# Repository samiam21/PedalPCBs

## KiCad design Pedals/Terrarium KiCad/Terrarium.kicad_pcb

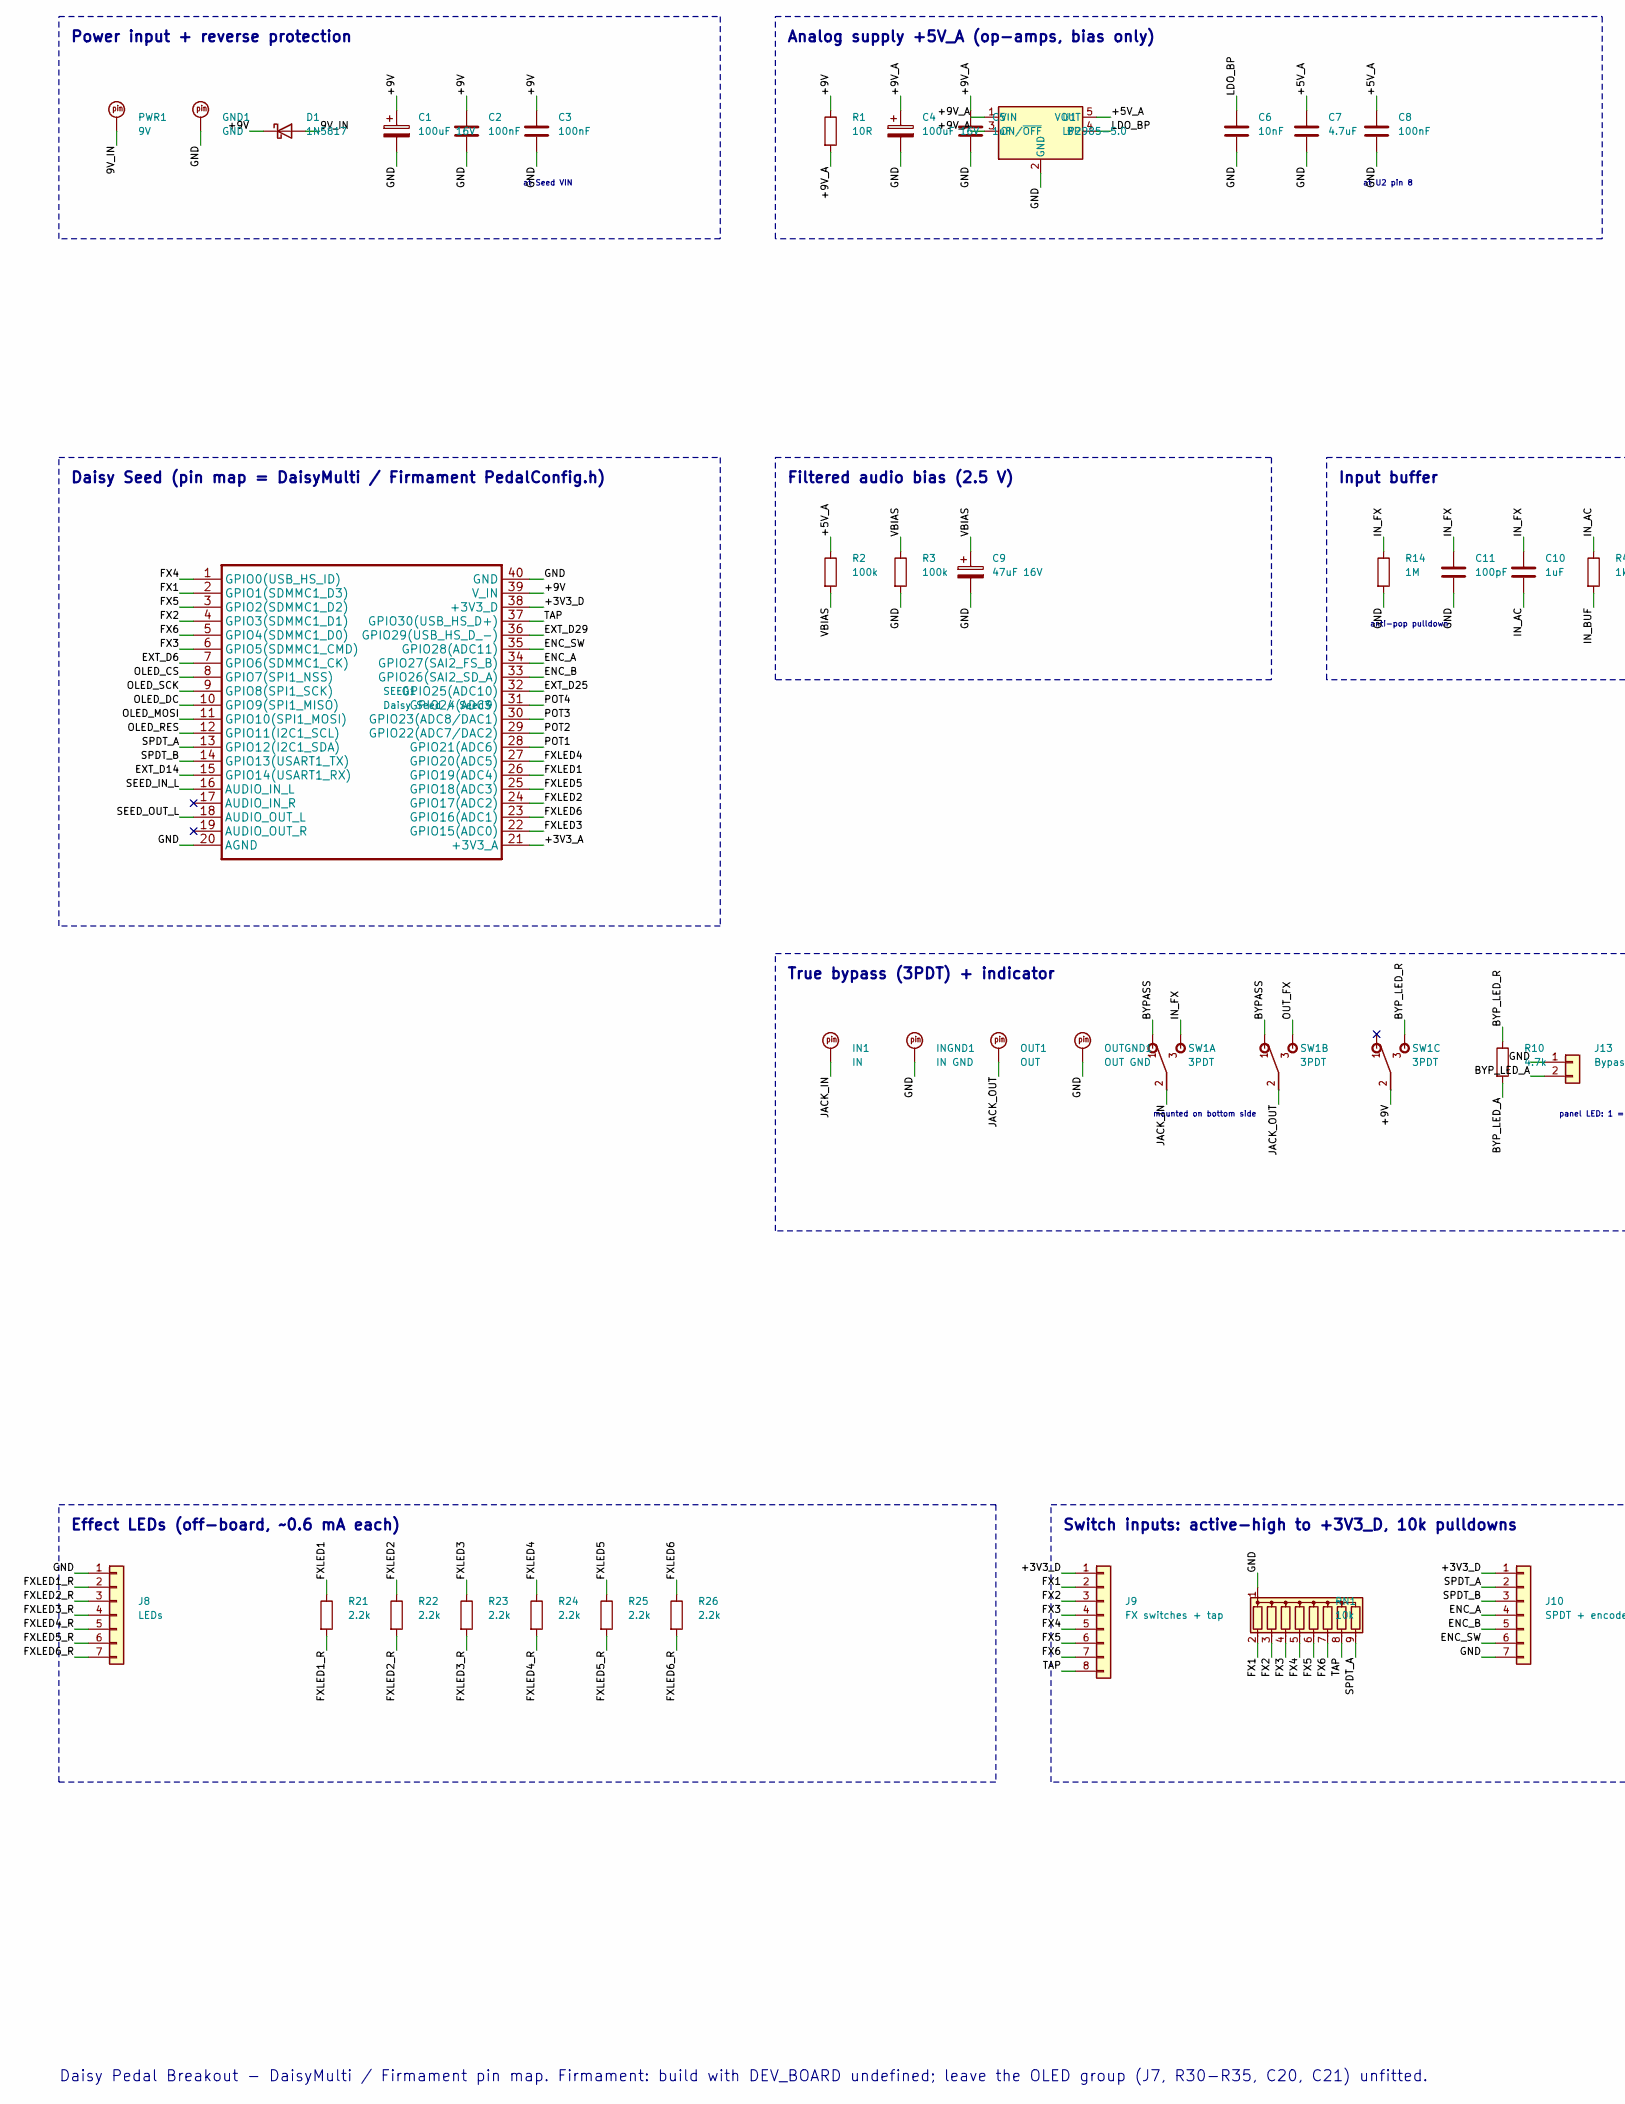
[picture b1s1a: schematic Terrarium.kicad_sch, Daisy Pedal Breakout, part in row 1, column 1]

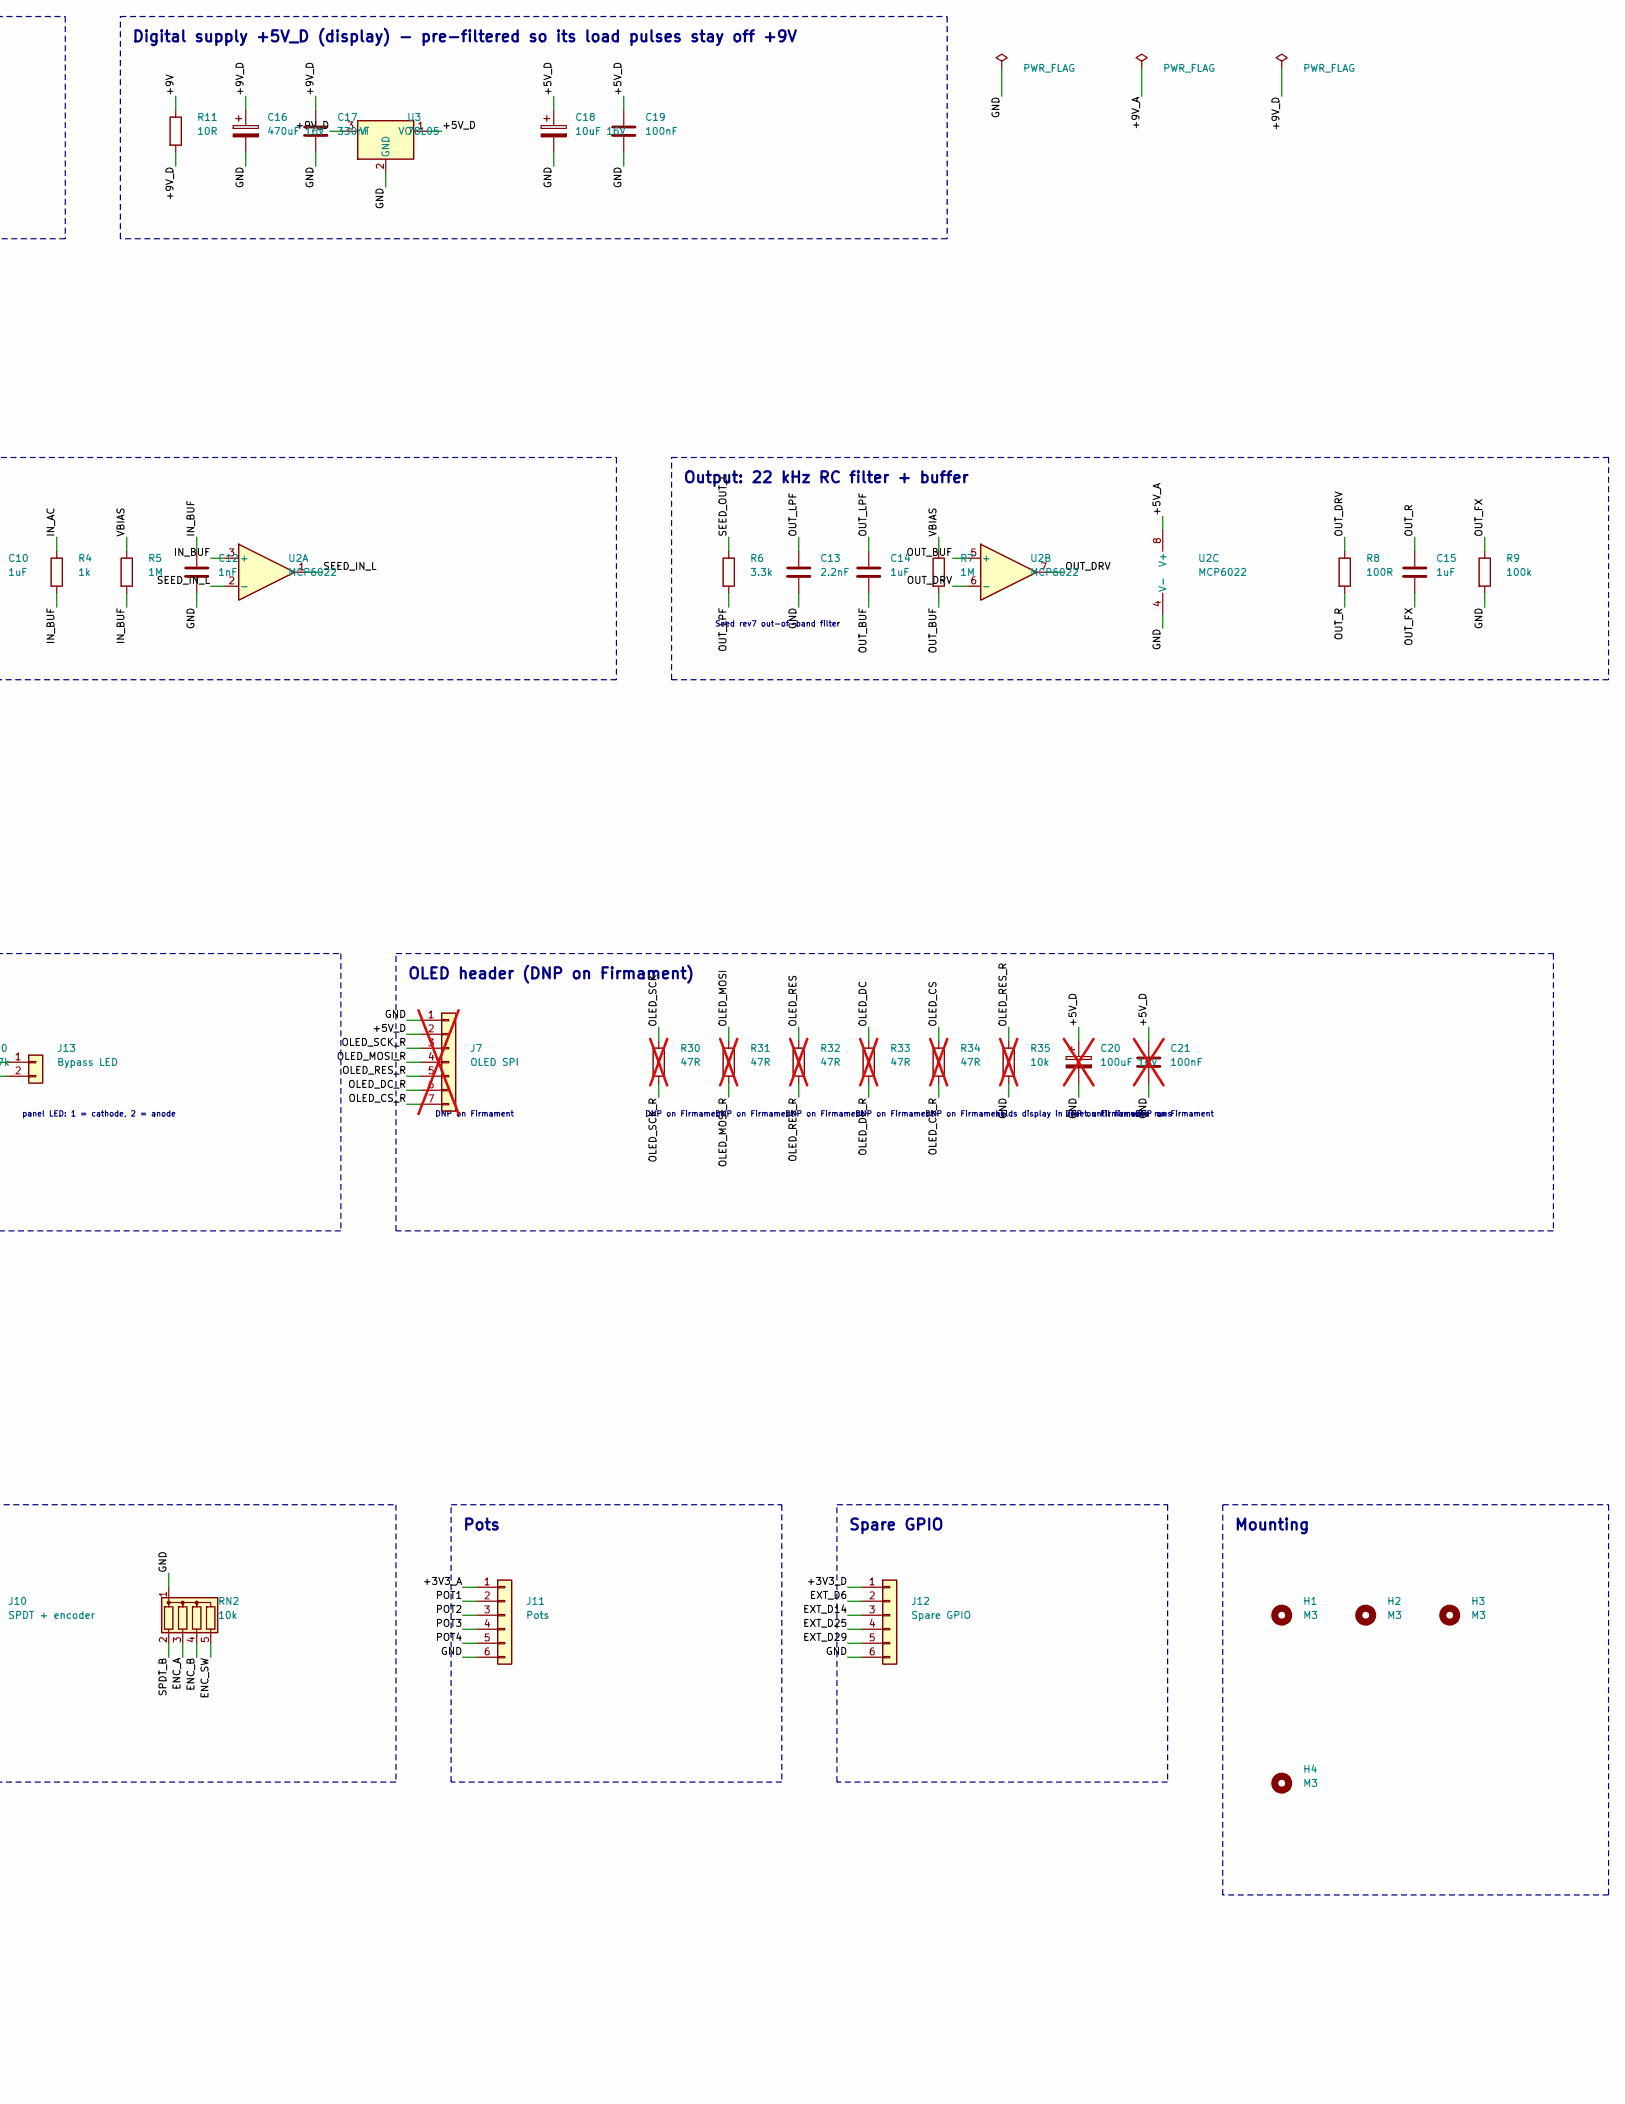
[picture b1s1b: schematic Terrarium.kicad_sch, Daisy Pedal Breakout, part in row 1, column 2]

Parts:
C1, C4: 100uF 16V; CP_Radial_D6.3mm_P2.50mm
C2, C3: 100nF; C_Disc_D5.0mm_W2.5mm_P5.00mm
C5: 1uF; C_Disc_D3.0mm_W1.6mm_P2.50mm
C6: 10nF; C_Disc_D3.0mm_W1.6mm_P2.50mm
C7: 4.7uF; C_Disc_D3.0mm_W1.6mm_P2.50mm
C8, C19: 100nF; C_Disc_D3.0mm_W1.6mm_P2.50mm
C9: 47uF 16V; CP_Radial_D5.0mm_P2.00mm
C10, C14, C15: 1uF; C_Rect_L7.2mm_W4.5mm_P5.00mm_FKS2_FKP2_MKS2_MKP2
C11: 100pF; C_Disc_D3.0mm_W1.6mm_P2.50mm
C12: 1nF; C_Disc_D3.0mm_W1.6mm_P2.50mm
C13: 2.2nF; C_Disc_D5.0mm_W2.5mm_P5.00mm
C16: 470uF 16V; CP_Radial_D8.0mm_P3.50mm
C17: 330nF; C_Disc_D5.0mm_W2.5mm_P5.00mm
C18: 10uF 16V; CP_Radial_D5.0mm_P2.00mm
C20: 100uF 16V; CP_Radial_D6.3mm_P2.50mm; not fitted
C21: 100nF; C_Disc_D3.0mm_W1.6mm_P2.50mm; not fitted
D1: 1N5817; D_DO-41_SOD81_P10.16mm_Horizontal
GND1: GND; UNLABELED
H1, H2, H3, H4: M3; MountingHole_3.2mm_M3
IN1: IN; UNLABELED
INGND1: IN GND; UNLABELED
J7: OLED SPI; PinHeader_1x07_P2.54mm_Vertical; not fitted
J8: LEDs; PinHeader_1x07_P2.54mm_Vertical
J9: FX switches + tap; PinHeader_1x08_P2.54mm_Vertical
J10: SPDT + encoder; PinHeader_1x07_P2.54mm_Vertical
J11: Pots; PinHeader_1x06_P2.54mm_Vertical
J12: Spare GPIO; PinHeader_1x06_P2.54mm_Vertical
J13: Bypass LED; PinHeader_1x02_P2.54mm_Vertical
OUT1: OUT; UNLABELED
OUTGND1: OUT GND; UNLABELED
PWR1: 9V; UNLABELED
R1, R11: 10R; R_Axial_DIN0207_L6.3mm_D2.5mm_P7.62mm_Horizontal
R2, R3, R9: 100k; R_Axial_DIN0207_L6.3mm_D2.5mm_P7.62mm_Horizontal
R4: 1k; R_Axial_DIN0207_L6.3mm_D2.5mm_P7.62mm_Horizontal
R5, R7, R14: 1M; R_Axial_DIN0207_L6.3mm_D2.5mm_P7.62mm_Horizontal
R6: 3.3k; R_Axial_DIN0207_L6.3mm_D2.5mm_P7.62mm_Horizontal
R8: 100R; R_Axial_DIN0207_L6.3mm_D2.5mm_P7.62mm_Horizontal
R10: 4.7k; R_Axial_DIN0207_L6.3mm_D2.5mm_P7.62mm_Horizontal
R21, R22, R23, R24, R25, R26: 2.2k; R_Axial_DIN0207_L6.3mm_D2.5mm_P7.62mm_Horizontal
R30, R31, R32, R33, R34: 47R; R_Axial_DIN0207_L6.3mm_D2.5mm_P2.54mm_Vertical; not fitted
R35: 10k; R_Axial_DIN0207_L6.3mm_D2.5mm_P2.54mm_Vertical; not fitted
RN1: 10k; R_Array_SIP9
RN2: 10k; R_Array_SIP5
SEED1: Daisy Seed / Seed3; ES_DAISY_SEED
SW1: 3PDT; 3PDT2
U1: LP2985-5.0; SOT-23-5
U2: MCP6022; DIP-8_W7.62mm
U3: 78L05; TO-92_Inline

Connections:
/9V_IN: D1.2 (A), PWR1.P$1
/+3V3_A: J11.1, SEED1.21 (+3V3_A)
/+3V3_D: J9.1, J10.1, J12.1, SEED1.38 (+3V3_D)
/+5V_A: C7.1, C8.1, R2.1, U1.5 (VOUT), U2.8 (V+)
/+5V_D: C18.1, C19.1, C20.1, C21.1, J7.2, U3.1 (VO)
/+9V: C1.1, C2.1, C3.1, D1.1 (K), R1.1, R11.1, SEED1.39 (V_IN), SW1.C2 (2)
/+9V_A: C4.1, C5.1, R1.2, U1.1 (VIN), U1.3 (ON/~OFF)
/+9V_D: C16.1, C17.1, R11.2, U3.3 (VI)
/BYPASS: SW1.A1 (1), SW1.B1 (1)
/BYP_LED_A: J13.2, R10.2
/BYP_LED_R: R10.1, SW1.C3 (3)
/ENC_A: J10.4, RN2.3 (R2), SEED1.34 (GPIO27(SAI2_FS_B))
/ENC_B: J10.5, RN2.4 (R3), SEED1.33 (GPIO26(SAI2_SD_A))
/ENC_SW: J10.6, RN2.5 (R4), SEED1.35 (GPIO28(ADC11))
/EXT_D6: J12.2, SEED1.7 (GPIO6(SDMMC1_CK))
/EXT_D14: J12.3, SEED1.15 (GPIO14(USART1_RX))
/EXT_D25: J12.4, SEED1.32 (GPIO25(ADC10))
/EXT_D29: J12.5, SEED1.36 (GPIO29(USB_HS_D_-))
/FX1: J9.2, RN1.2 (R1), SEED1.2 (GPIO1(SDMMC1_D3))
/FX2: J9.3, RN1.3 (R2), SEED1.4 (GPIO3(SDMMC1_D1))
/FX3: J9.4, RN1.4 (R3), SEED1.6 (GPIO5(SDMMC1_CMD))
/FX4: J9.5, RN1.5 (R4), SEED1.1 (GPIO0(USB_HS_ID))
/FX5: J9.6, RN1.6 (R5), SEED1.3 (GPIO2(SDMMC1_D2))
/FX6: J9.7, RN1.7 (R6), SEED1.5 (GPIO4(SDMMC1_D0))
/FXLED1: R21.1, SEED1.26 (GPIO19(ADC4))
/FXLED1_R: J8.2, R21.2
/FXLED2: R22.1, SEED1.24 (GPIO17(ADC2))
/FXLED2_R: J8.3, R22.2
/FXLED3: R23.1, SEED1.22 (GPIO15(ADC0))
/FXLED3_R: J8.4, R23.2
/FXLED4: R24.1, SEED1.27 (GPIO20(ADC5))
/FXLED4_R: J8.5, R24.2
/FXLED5: R25.1, SEED1.25 (GPIO18(ADC3))
/FXLED5_R: J8.6, R25.2
/FXLED6: R26.1, SEED1.23 (GPIO16(ADC1))
/FXLED6_R: J8.7, R26.2
/GND: C1.2, C2.2, C3.2, C4.2, C5.2, C6.2, C7.2, C8.2, C9.2, C11.2, C12.2, C13.2, C16.2, C17.2, C18.2, C19.2, C20.2, C21.2, GND1.P$1, INGND1.P$1, J7.1, J8.1, J10.7, J11.6, J12.6, J13.1, OUTGND1.P$1, R3.2, R9.2, R14.2, R35.2, RN1.1 (common), RN2.1 (common), SEED1.20 (AGND), SEED1.40 (GND), U1.2 (GND), U2.4 (V-), U3.2 (GND)
/IN_AC: C10.2, R4.1
/IN_BUF: C12.1, R4.2, R5.2, U2.3 (+)
/IN_FX: C10.1, C11.1, R14.1, SW1.A3 (3)
/JACK_IN: IN1.P$1, SW1.A2 (2)
/JACK_OUT: OUT1.P$1, SW1.B2 (2)
/LDO_BP: C6.1, U1.4 (BP)
/OLED_CS: R34.1, SEED1.8 (GPIO7(SPI1_NSS))
/OLED_CS_R: J7.7, R34.2
/OLED_DC: R33.1, SEED1.10 (GPIO9(SPI1_MISO))
/OLED_DC_R: J7.6, R33.2
/OLED_MOSI: R31.1, SEED1.11 (GPIO10(SPI1_MOSI))
/OLED_MOSI_R: J7.4, R31.2
/OLED_RES: R32.1, SEED1.12 (GPIO11(I2C1_SCL))
/OLED_RES_R: J7.5, R32.2, R35.1
/OLED_SCK: R30.1, SEED1.9 (GPIO8(SPI1_SCK))
/OLED_SCK_R: J7.3, R30.2
/OUT_BUF: C14.2, R7.2, U2.5 (+)
/OUT_DRV: R8.1, U2.6 (-), U2.7
/OUT_FX: C15.2, R9.1, SW1.B3 (3)
/OUT_LPF: C13.1, C14.1, R6.2
/OUT_R: C15.1, R8.2
/POT1: J11.2, SEED1.28 (GPIO21(ADC6))
/POT2: J11.3, SEED1.29 (GPIO22(ADC7/DAC2))
/POT3: J11.4, SEED1.30 (GPIO23(ADC8/DAC1))
/POT4: J11.5, SEED1.31 (GPIO24(ADC9))
/SEED_IN_L: SEED1.16 (AUDIO_IN_L), U2.1, U2.2 (-)
/SEED_OUT_L: R6.1, SEED1.18 (AUDIO_OUT_L)
/SPDT_A: J10.2, RN1.9 (R8), SEED1.13 (GPIO12(I2C1_SDA))
/SPDT_B: J10.3, RN2.2 (R1), SEED1.14 (GPIO13(USART1_TX))
/TAP: J9.8, RN1.8 (R7), SEED1.37 (GPIO30(USB_HS_D+))
/VBIAS: C9.1, R2.2, R3.1, R5.1, R7.1

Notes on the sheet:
at Seed VIN
Power input + reverse protection
at U2 pin 8
Analog supply +5V_A (op-amps, bias only)
Digital supply +5V_D (display) - pre-filtered so its load pulses stay off +9V
Daisy Seed (pin map = DaisyMulti / Firmament PedalConfig.h)
Filtered audio bias (2.5 V)
anti-pop pulldown
Input buffer
Seed rev7 out-of-band filter
Output: 22 kHz RC filter + buffer
mounted on bottom side
panel LED: 1 = cathode, 2 = anode
True bypass (3PDT) + indicator
DNP on Firmament
holds display in reset until firmware runs
OLED header (DNP on Firmament)
Effect LEDs (off-board, ~0.6 mA each)
Switch inputs: active-high to +3V3_D, 10k pulldowns
Pots
Spare GPIO
Mounting
Daisy Pedal Breakout - DaisyMulti / Firmament pin map. Firmament: build with DEV_BOARD undefined; leave the OLED group (J7, R30-R35, C20, C21) unfitted.

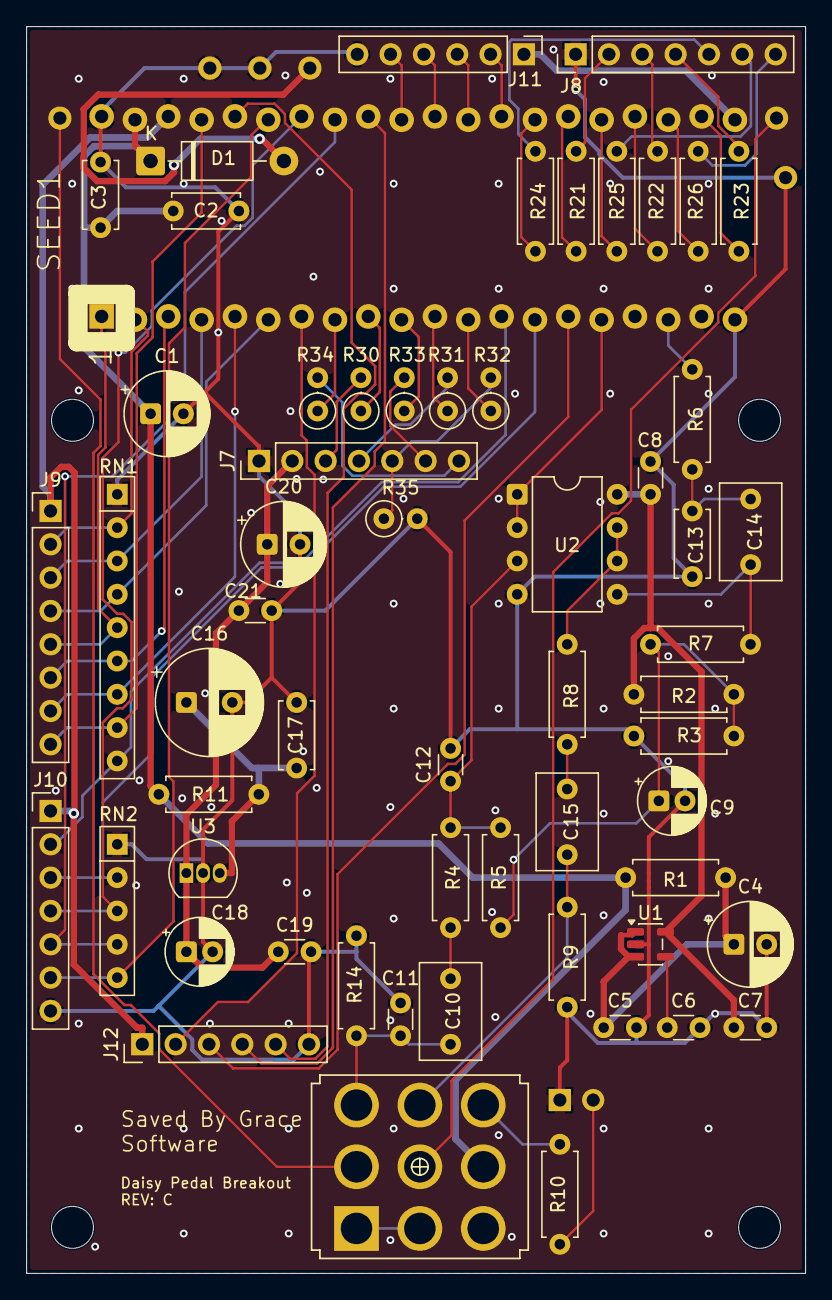
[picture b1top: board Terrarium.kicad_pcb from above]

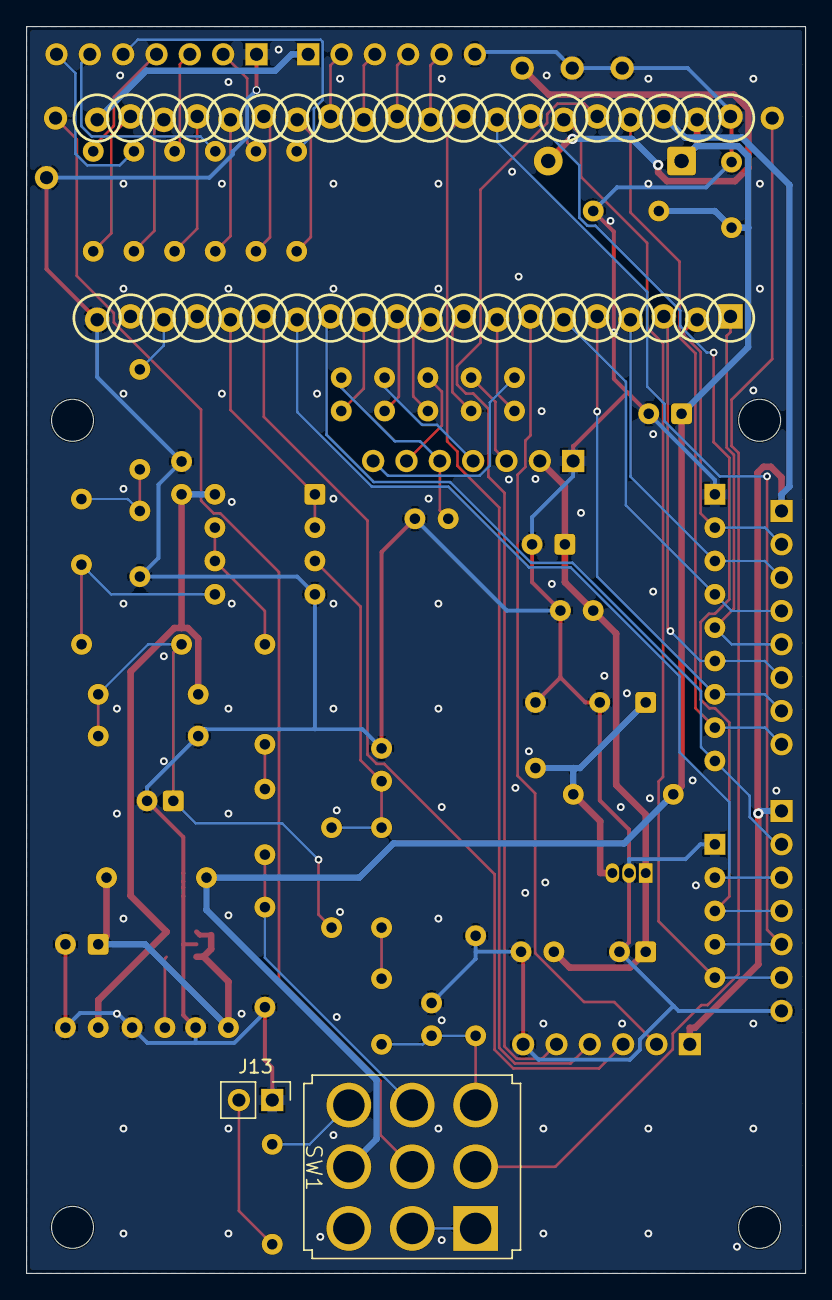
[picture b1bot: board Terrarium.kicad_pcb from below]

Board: 2 copper layers, 59.4 x 95.0 mm, 70 parts (2 on the bottom side), 68 nets.

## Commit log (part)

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2021-03-31 Add eagle libraries and initial zdrive
2021-03-31 Update zdrive schematic with new pots
2021-03-31 Add zdrive reference docs
2021-03-31 Update schematic and begin board layout
2021-03-31 Working on layout
2021-04-01 Remove accidental folder commit
2021-04-01 Adding switch for capacitor
2021-04-01 Working on board layout
2021-04-07 Restarting board design...
2021-04-07 Re-add reference docs
2021-04-13 Working on routing
2021-04-13 Board routed V1
2021-04-15 Shift switch
2021-04-16 Adjusted the pots
2021-04-19 Rotate switch
2021-04-22 Shift pots so they are centered
2021-04-22 Update silkscreen
2021-04-28 Add bypass schematic
2021-04-28 Route board
2021-05-10 Update switch to correct footprint size
2021-05-11 Switch pots to bottom and add gnd plane
2021-05-12 Flip top pots
2021-05-12 Flip bottom pots
2021-05-12 Push to Fusion
2021-06-11 Flipped the volume and tone pots
2021-06-11 Fix labels on board
2021-06-11 Move resistor for greater impact of switch
2021-07-27 Add parts to library
2021-07-27 Add digilent schematic
2021-07-27 Add grounding planes
2021-07-27 Round corners
2021-07-27 Update board label
2021-08-17 Add Analog Discovery 2 header to library
2021-08-23 DP-97 - Move breakout board to this repo
2021-08-23 DP-97 - Update with wave analysis board
2021-08-23 DP-97 - Add DIP switch to library
2021-09-29 Put correct header on the digilent PCB
2021-09-29 DP-97 - Update multi-effect grounding scheme
2021-09-29 DP-97 - Finish updating grounding scheme on multi-effect pedal
2021-10-06 DP-97 - Add power conditioning caps to 3V3_D
2023-03-11 Updated to larger cap footprints for Headmaster
2023-03-27 Removed transistors
2023-03-29 Add Electrosmith library
2023-03-29 Add more libraries
2023-03-29 Start Terrarium schematic
2023-04-03 Updating schematic
2023-04-03 Finish base schematic
2023-04-03 Begin board layout
2023-04-03 Fix capacitor sizes
2023-04-04 Update parts and place them on the board
2023-04-04 Finished terrarium board routing
2023-04-05 Add true bypass
2023-04-05 Add the Terrarium PDF
2023-04-11 Revert headmaster to correct revision
2023-04-11 Update capacitors to be larger size
2023-05-08 Fix true bypass circuit on Terrarium
2023-05-08 Fix silkscreen on Terrarium
